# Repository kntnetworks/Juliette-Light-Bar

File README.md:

# Project Overview

 This repository contains the KiCad design files for a replacement Printed Circuit Board (PCB) for the lighted band indicators in the ** *Juliette 5-Band, 18-Transistor Radio* **. The primary goal of this project is to replace the original band select PCB, which utilizes fuse style lamps, with 5mm LEDs and associated Current Limiting Resistors (CLRs).

I created this KiCad project for a restoration effort.  This Juliette radio contains a small PCB that is populated with fuse style lights, holders, and power connections from the band selection switch.  This provides a lighted band indicator on the bottom front of the radio. The radio under restoration 
suffered from leaking battery acid which had corroded the PCB to the point that it was not salvageable.  

## Getting Started

To view, modify, or fabricate this PCB, you will need to install [KiCad](https://www.kicad.org/), a free and open-source EDA suite.  

## Main Files 
- **Juliette Light Bar.kicad_sch** - this file is the schematic showing the symbols and electrical connections of the circuit. Note that mounting hole symbols are included in the schematic. Since mounting holes sometimes include copper pads for connectivity (e.g., circuit grounds) KiCad requires them to be added to the schematic so they can be placed as a footprint on the PCB.
- **Juliette Light Bar.kicad_pcb** - this is the PCB layout file that contains the component footprints including copper pads and traces.

Although this PCB can be exported and sent to a fab house for production, I have modified the footprints and traces with the goal of creating my own PCB at home with copper-clad board and the "toner-transfer" method of PCB creation.  

A great tutorial of this method can be found here:
https://www.youtube.com/embed/aemG_4sDz_Q?si=_ouqTl-AMnO7pNbh

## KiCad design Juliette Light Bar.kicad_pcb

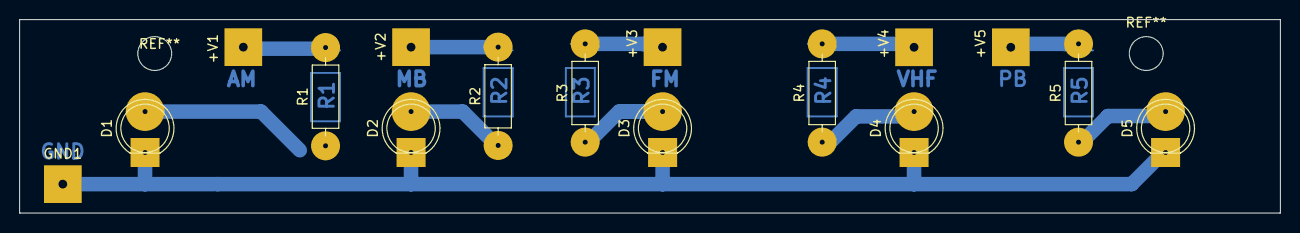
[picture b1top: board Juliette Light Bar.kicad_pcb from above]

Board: 2 copper layers, 130.3 x 20.0 mm, 16 parts (0 on the bottom side), 11 nets.

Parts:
+V1: Conn_01x01_Socket; SolderWire-1.5sqmm_1x01_D1.7mm_OD3.9mm
+V2, +V3, +V4, +V5: Conn_01x01; SolderWire-1.5sqmm_1x01_D1.7mm_OD3.9mm
D1, D2, D3, D4, D5: LED_5mm; LED_D5.0mm
GND1: Conn_01x01; SolderWire-1.5sqmm_1x01_D1.7mm_OD3.9mm
R1, R2, R3, R4, R5: 1.2k; R_Axial_DIN0207_L6.3mm_D2.5mm_P10.16mm_Horizontal

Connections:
GND: D1.1, D2.1, D3.1, D4.1, D5.1, GND1.1
unnamed: +V1.1, R1.2
unnamed: +V2.1, R2.2
unnamed: +V3.1, R3.2
unnamed: +V4.1, R4.2
unnamed: +V5.1, R5.2
unnamed: D1.2, R1.1
unnamed: D2.2, R2.1
unnamed: D3.2, R3.1
unnamed: D4.2, R4.1
unnamed: D5.2, R5.1
